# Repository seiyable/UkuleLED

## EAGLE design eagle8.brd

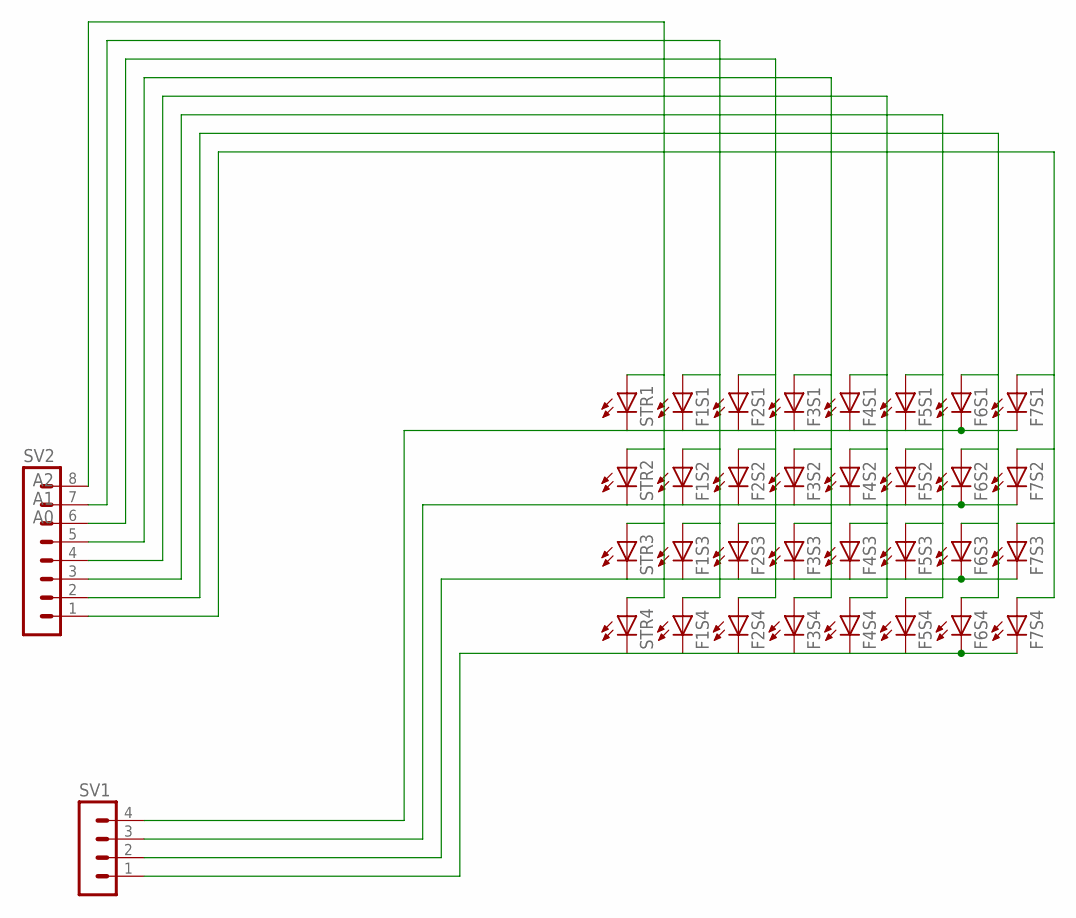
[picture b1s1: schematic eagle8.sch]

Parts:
F1S1, F1S2, F1S3, F1S4, F2S1, F2S2, F2S3, F2S4, F3S1, F3S2, F3S3, F3S4, F4S1, F4S2, F4S3, F4S4, F5S1, F5S2, F5S3, F5S4, F6S1, F6S2, F6S3, F6S4, F7S1, F7S2, F7S3, F7S4: LED_ESML0603; LED_SML0603
STR1, STR2, STR3, STR4: LED_ESML0603; LED_SML0603
SV1: MA04-1
SV2: MA08-1

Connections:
A0: F2S1.A, F2S2.A, F2S3.A, F2S4.A, SV2.6
A1: F1S1.A, F1S2.A, F1S3.A, F1S4.A, SV2.7
A2: STR1.A, STR2.A, STR3.A, STR4.A, SV2.8
unnamed: F1S3.C, F2S3.C, F3S3.C, F4S3.C, F5S3.C, F6S3.C, F7S3.C, STR3.C, SV1.2
unnamed: F1S2.C, F2S2.C, F3S2.C, F4S2.C, F5S2.C, F6S2.C, F7S2.C, STR2.C, SV1.3
unnamed: F1S1.C, F2S1.C, F3S1.C, F4S1.C, F5S1.C, F6S1.C, F7S1.C, STR1.C, SV1.4
unnamed: F7S1.A, F7S2.A, F7S3.A, F7S4.A, SV2.1
unnamed: F6S1.A, F6S2.A, F6S3.A, F6S4.A, SV2.2
unnamed: F4S1.A, F4S2.A, F4S3.A, F4S4.A, SV2.4
unnamed: F3S1.A, F3S2.A, F3S3.A, F3S4.A, SV2.5
unnamed: F1S4.C, F2S4.C, F3S4.C, F4S4.C, F5S4.C, F6S4.C, F7S4.C, STR4.C, SV1.1
unnamed: F5S1.A, F5S2.A, F5S3.A, F5S4.A, SV2.3

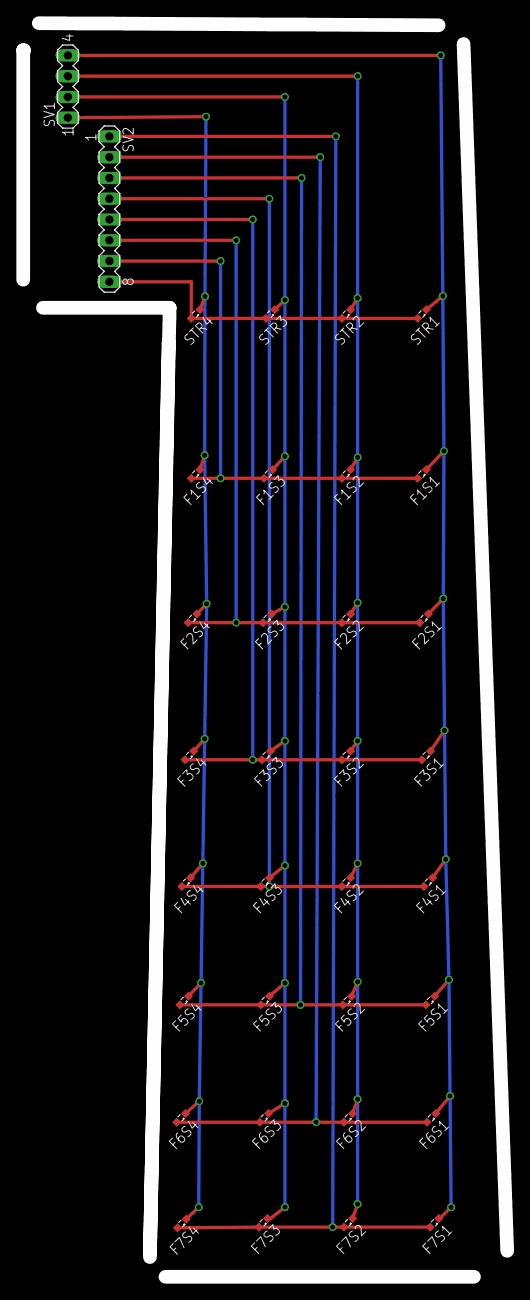
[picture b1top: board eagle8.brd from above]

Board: 2 copper layers, 59.2 x 153.3 mm, 34 parts (0 on the bottom side), 12 nets.

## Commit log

2015-04-20 changed parcing function
2015-04-22 modified for user testing
2015-04-22 Eagle file
2015-04-22 added eagle files
2015-04-22 re-organized directories
2015-04-22 cleaned up
2015-04-22 clean up
2015-04-29 eagle files added
